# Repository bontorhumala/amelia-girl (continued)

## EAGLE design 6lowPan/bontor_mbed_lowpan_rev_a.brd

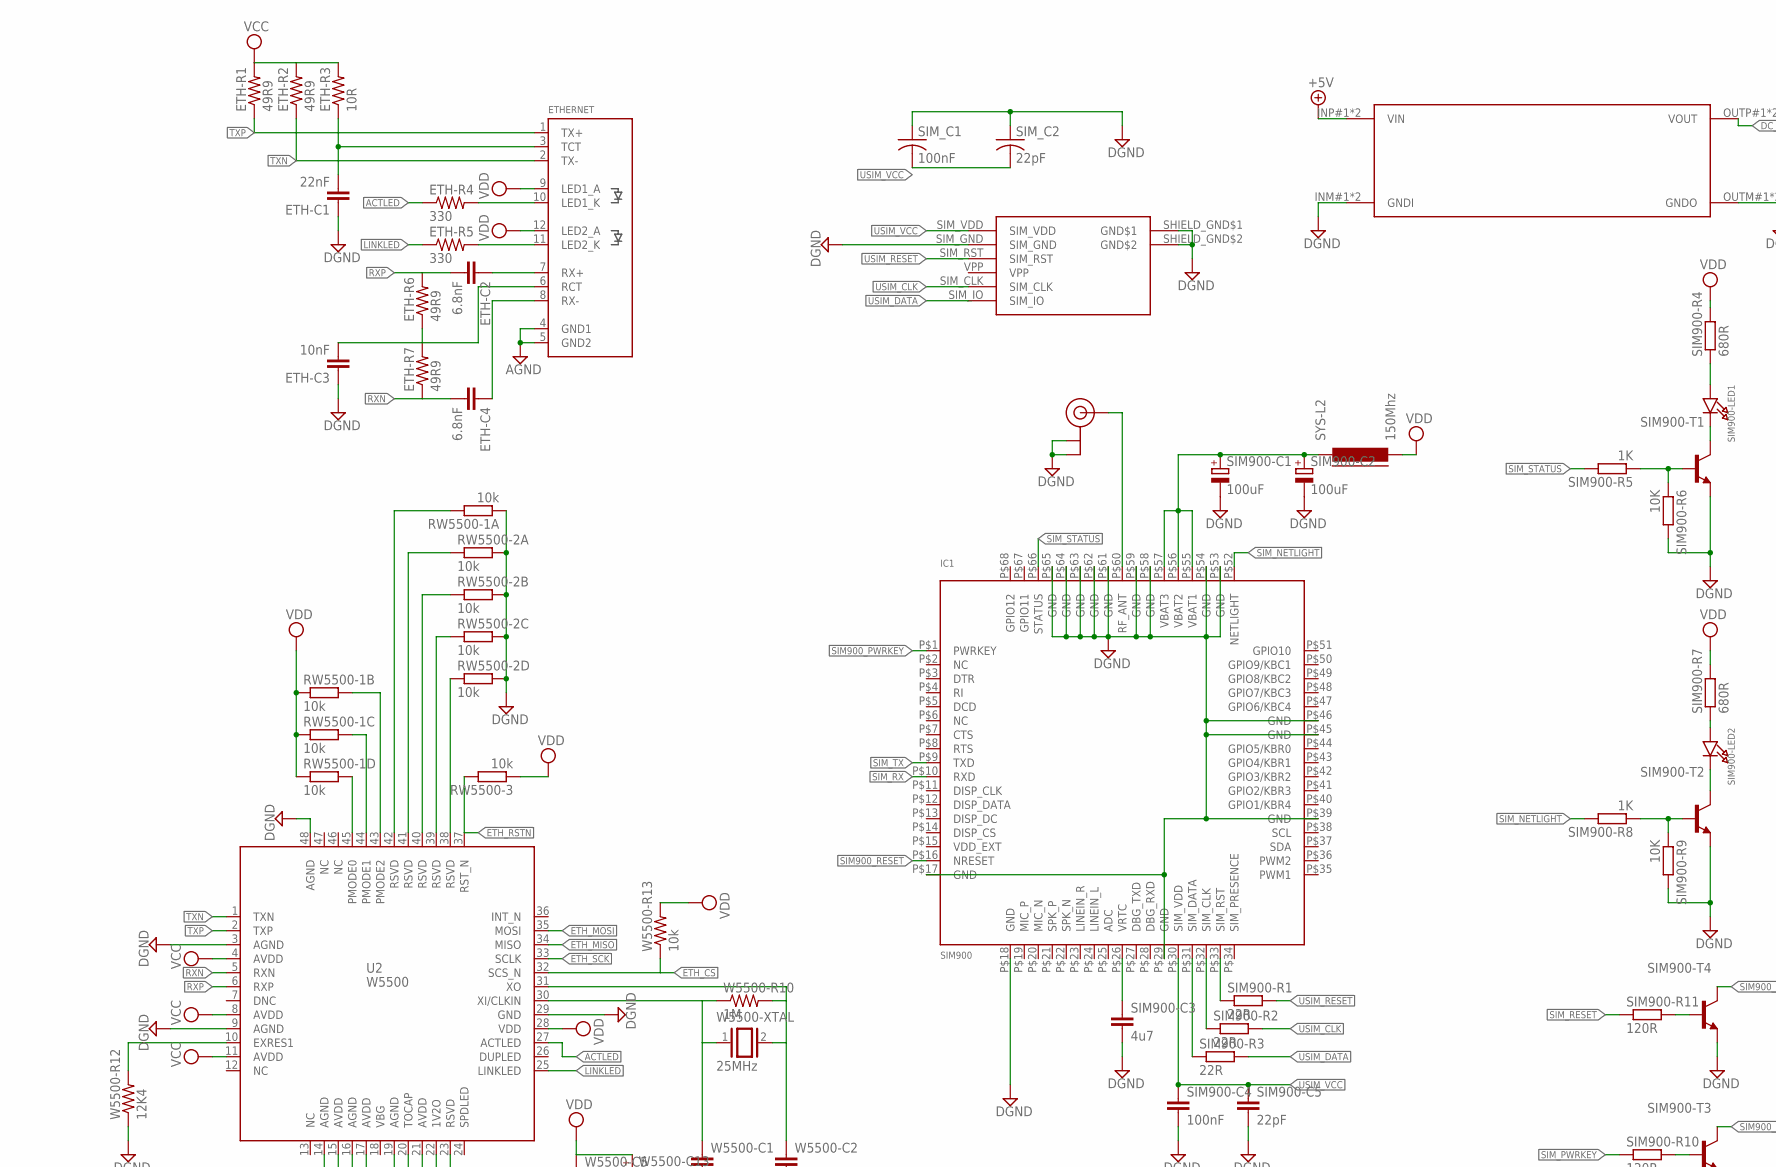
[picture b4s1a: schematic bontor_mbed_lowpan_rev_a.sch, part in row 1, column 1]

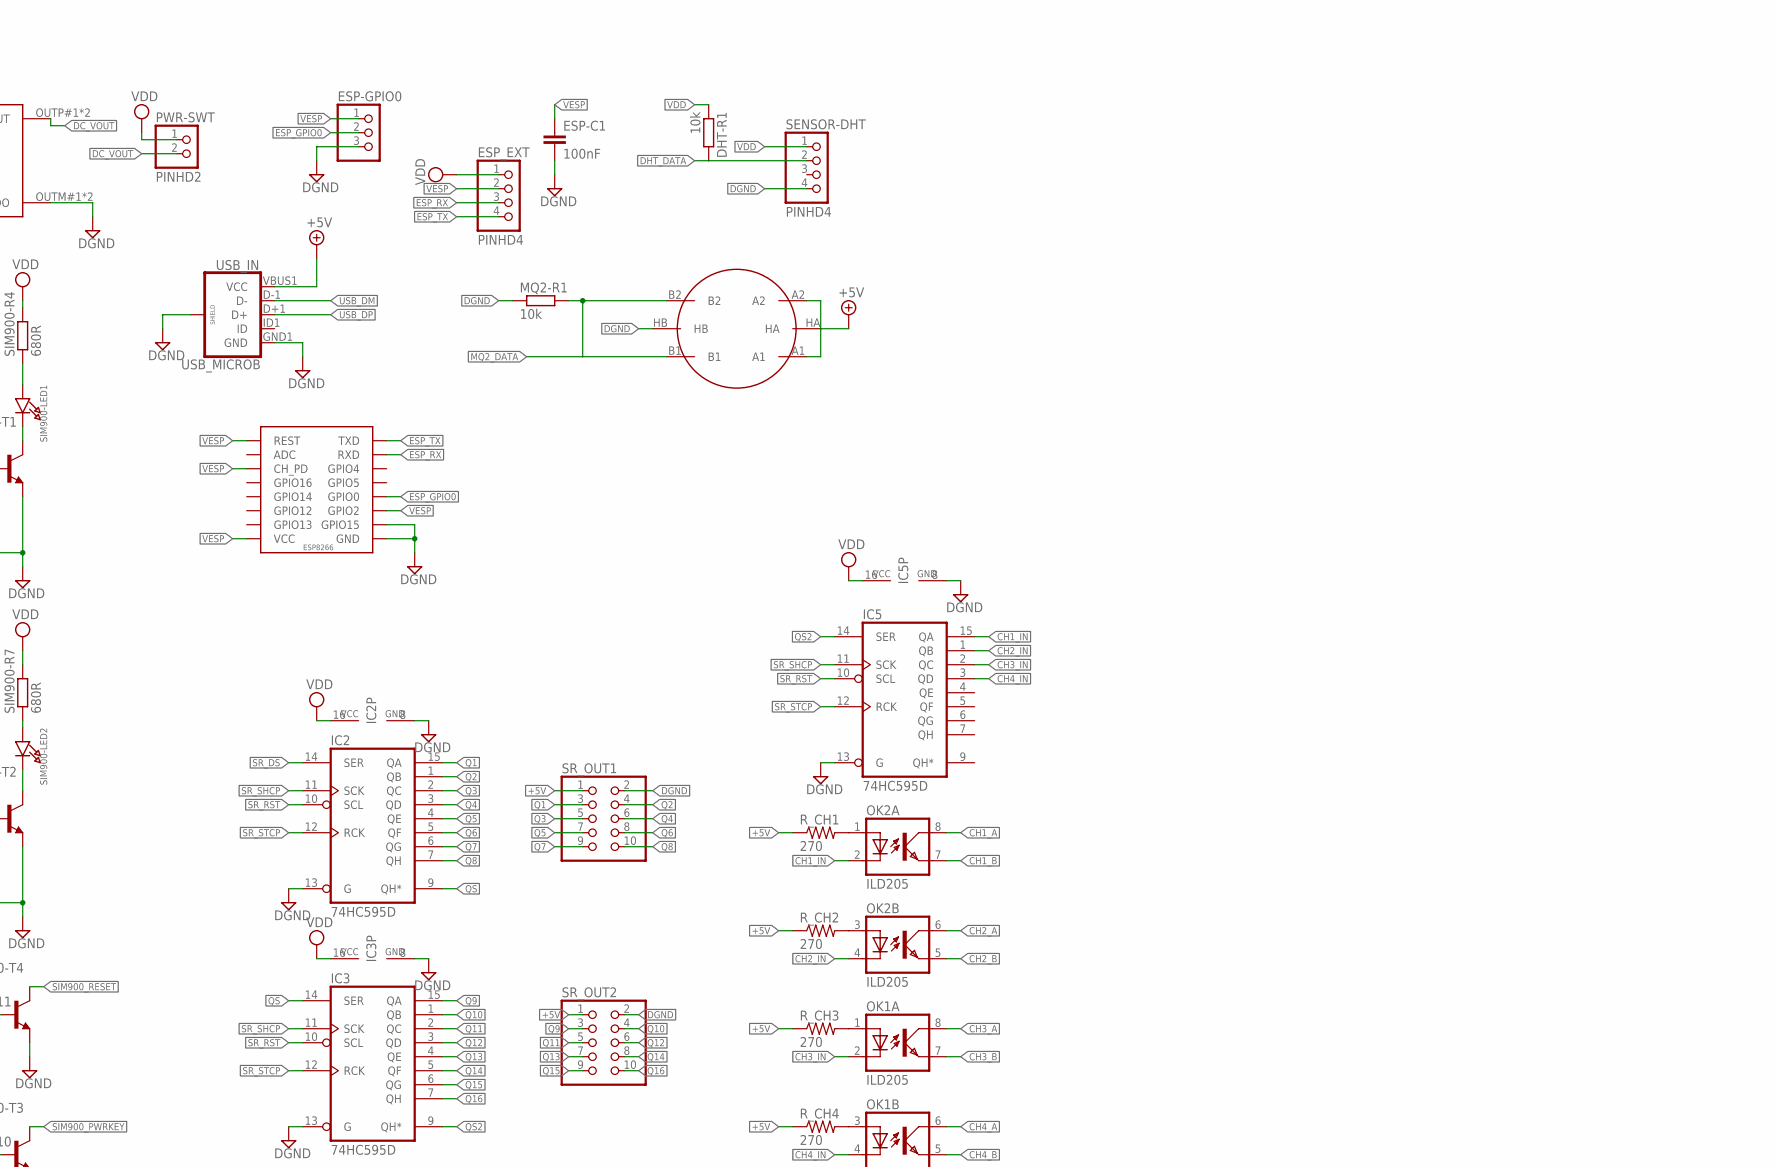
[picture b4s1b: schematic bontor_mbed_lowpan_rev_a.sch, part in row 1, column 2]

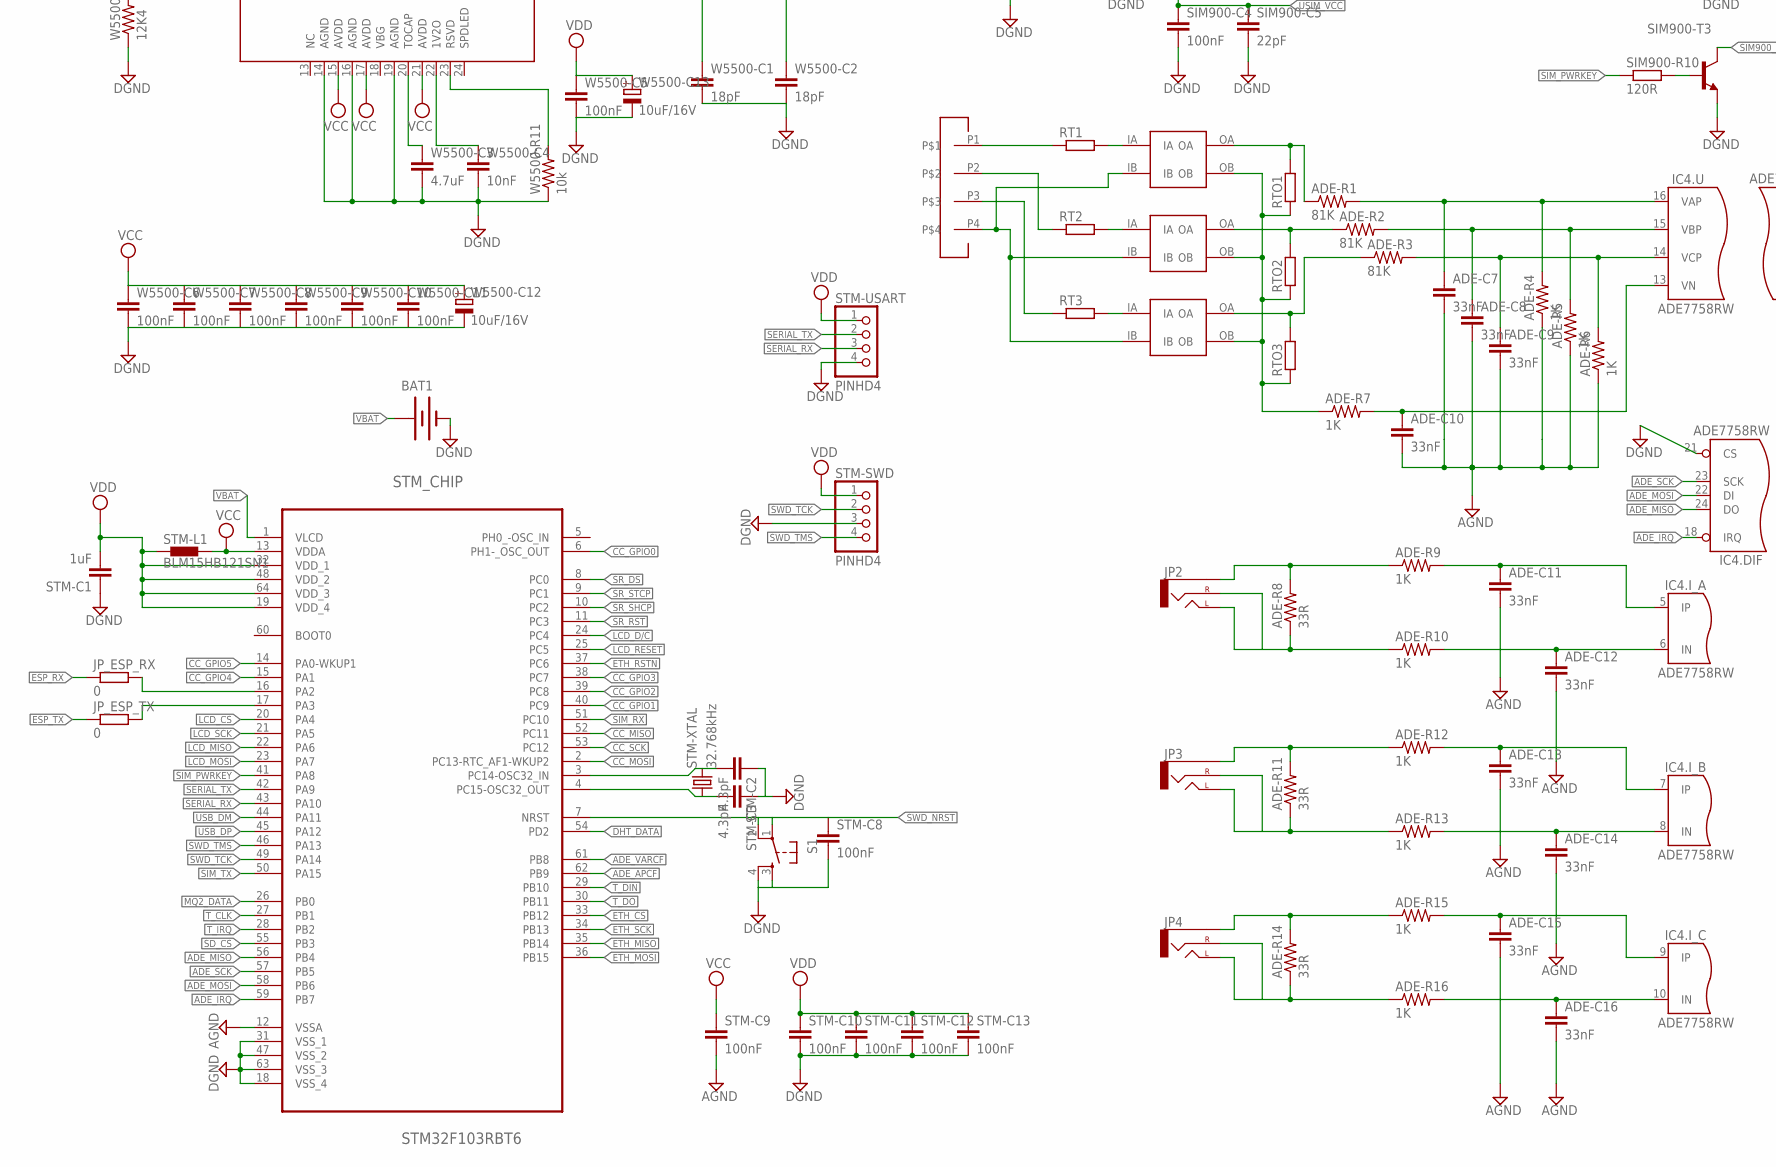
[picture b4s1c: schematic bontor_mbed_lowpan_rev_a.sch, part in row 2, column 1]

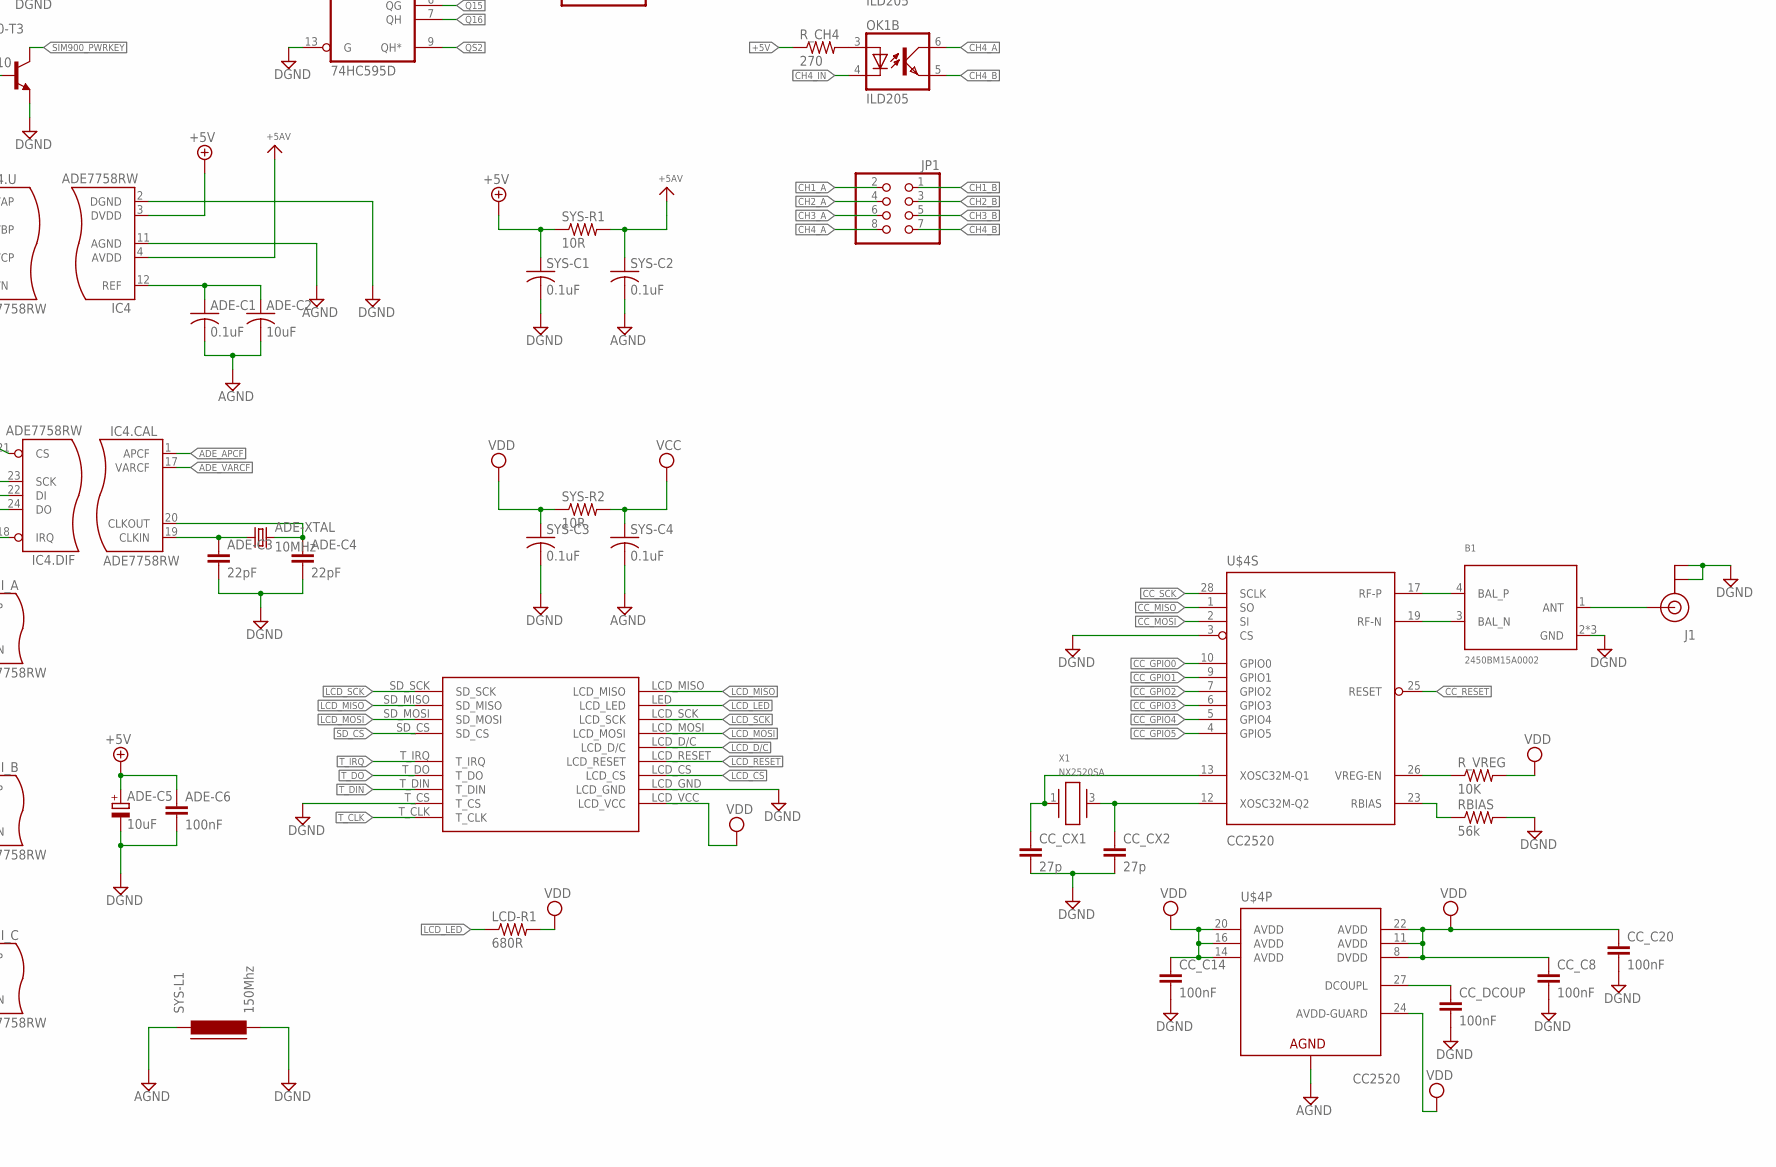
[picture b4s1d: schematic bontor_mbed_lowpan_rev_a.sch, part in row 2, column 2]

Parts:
ADE-C1: 0.1uF; C0603@1
ADE-C2: 10uF; C0805K
ADE-C3, ADE-C4: 22pF; C0603
ADE-C5: 10uF; 153CLV-0605
ADE-C6: 100nF; C0603
ADE-C7, ADE-C8, ADE-C9, ADE-C10, ADE-C11, ADE-C12, ADE-C13, ADE-C14, ADE-C15, ADE-C16: 33nF; 0603-CAP
ADE-R1, ADE-R2, ADE-R3: 81K; 0603-RES
ADE-R4, ADE-R5, ADE-R6, ADE-R7, ADE-R9, ADE-R10, ADE-R12, ADE-R13, ADE-R15, ADE-R16: 1K; 0603-RES
ADE-R8, ADE-R11, ADE-R14: 33R; 0603-RES
ADE-XTAL: 10MHz; HC49US
B1: 2450BM15A0002; 2450BM
BAT1: BATTERY12MM; BATTCON_12MM
CC_C8, CC_C14, CC_C20: 100nF; C0402
CC_CX1, CC_CX2: 27p; C0201
CC_DCOUP: 100nF; C0402
DCDC-3.5V: DCDCMODULE_SMALL; DCDCMODULE-SMALL
DHT-R1: 10k; R0603
ESP-C1: 100nF; C0603
ESP-GPIO0: PINHD-1X3; 1X03
ESP_EXT: PINHD4
ETH-C1: 22nF; C0603
ETH-C2, ETH-C4: 6.8nF; C0603
ETH-C3: 10nF; C0603
ETH-R1, ETH-R2, ETH-R6, ETH-R7: 49R9; R0603
ETH-R3: 10R; R0603
ETH-R4, ETH-R5: 330; R0603
ETHERNET: RJ45J0026D21BNL; RJ45_PULSEJACK
IC1: SIM900; SIM900_SMT
IC2, IC3, IC5: 74HC595D; SO16
IC4: ADE7758RW; SOIC24
J1: U.FL
JP1: PINHD-2X4; 2X04
JP2, JP3, JP4: AUDIO-JACKSMD2; AUDIO-JACK-3.5MM-SMD
JP_ESP_RX: 0; R0201
JP_ESP_TX: 0; R0201
LCD-R1: 680R; 0603-RES
MQ2-R1: 10k; R0603
OK1, OK2: ILD205; SOIC08
PWR-SWT: PINHD2
RBIAS: 56k; 0402-RES
RT1, RT2, RT3: R-EU_0309/V; 0309V
RTO1, RTO2, RTO3: R-EU_0309/12; 0309/12
RW5500-1, RW5500-2: 10k; RN8P-4R-CRA06S
RW5500-3: 10k; R0603
R_CH1, R_CH2, R_CH3, R_CH4: 270; 0603-RES
R_VREG: 10K; 0402-RES
S1: TAC_SWITCHSMD; TACTILE-SWITCH-SMD
SENSOR-DHT: PINHD4
SENSOR-MQ2: METHANE_SENSOR; MQ-3
SIM900-C1, SIM900-C2: 100uF; 153CLV-0605
SIM900-C3: 4u7; C0603
SIM900-C4: 100nF; C0603
SIM900-C5: 22pF; C0603
SIM900-LED1, SIM900-LED2: LED0805_NOOUTLINE; CHIPLED_0805_NOOUTLINE
SIM900-R1, SIM900-R2, SIM900-R3: 22R; R0603
SIM900-R4, SIM900-R7: 680R; R0603
SIM900-R5, SIM900-R8: 1K; R0603
SIM900-R6, SIM900-R9: 10K; R0603
SIM900-R10, SIM900-R11: 120R; R0603
SIM900-T1, SIM900-T2, SIM900-T3, SIM900-T4: MMBT2222ALT1-NPN-SOT23-BEC; SOT23-BEC
SIM_C1: 100nF; C0603K
SIM_C2: 22pF; C0603K
SR_OUT1, SR_OUT2: PINHD-2X5/90; 2X05/90
STM-C1: 1uF; C0603
STM-C2, STM-C3: 4.3pF; C0603
STM-C8, STM-C9, STM-C10, STM-C11, STM-C12, STM-C13: 100nF; C0603
STM-L1: BLM15HB121SN1; 0402
STM-SWD: PINHD4
STM-USART: PINHD4
STM-XTAL: 32.768kHz; TC26H
STM_CHIP: STM32F103RBT6; QFP50P1200X1200X160-64N
SYS-C1, SYS-C2, SYS-C3, SYS-C4: 0.1uF; C0603@1
SYS-L1, SYS-L2: 150Mhz; FB805
SYS-R1, SYS-R2: 10R; 0603-RES
U2: W5500
U$4: CC2520; QFN50P500X500X100-29N
U$5: ESP8266WI12; WI12
U$7: U.FL
U$8: SIM_HOLDER; SIMHOLDER-PUSHPUSH
U$9, U$10, U$11: TRANSFORMER; TV16
U$12: TERMINAL_BLOCK; TERMINAL-RIGHT-ANGLE
U$13: LCD_2.4; LCD_TOUCH_2-4
USB_IN: USB_MICROB; USB-B-MICRO-SMD_V03
W5500-C1, W5500-C2: 18pF; C0603
W5500-C3: 4.7uF; C0603
W5500-C4: 10nF; C0603
W5500-C5, W5500-C6, W5500-C7, W5500-C8, W5500-C9, W5500-C10, W5500-C11: 100nF; C0603
W5500-C12, W5500-C13: 10uF/16V; 153CLV-0605
W5500-R10: 1M; R0603
W5500-R11, W5500-R13: 10k; R0603
W5500-R12: 12K4; R0805
W5500-XTAL: 25MHz; QS
X1: NX2520SA

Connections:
+5V: ADE-C5.+, ADE-C6.1, DCDC-3.5V.INP#1 (VIN), DCDC-3.5V.INP#2 (VIN), IC4.3 (DVDD), R_CH1.1, R_CH2.1, R_CH3.1, R_CH4.1, SENSOR-MQ2.A1, SENSOR-MQ2.A2, SENSOR-MQ2.HA, SR_OUT1.1, SR_OUT2.1, SYS-C1.1, SYS-R1.1, USB_IN.VBUS1 (VCC)
ACTLED: ETH-R4.1, U2.27 (ACTLED)
ADE_APCF: IC4.1 (APCF), STM_CHIP.62 (PB9)
ADE_IRQ: IC4.18 (IRQ), STM_CHIP.59 (PB7)
ADE_MISO: IC4.24 (DO), STM_CHIP.56 (PB4)
ADE_MOSI: IC4.22 (DI), STM_CHIP.58 (PB6)
ADE_SCK: IC4.23 (SCK), STM_CHIP.57 (PB5)
ADE_VARCF: IC4.17 (VARCF), STM_CHIP.61 (PB8)
AGND: ADE-C1.2, ADE-C2.2, ADE-C7.2, ADE-C8.2, ADE-C9.2, ADE-C10.2, ADE-C11.2, ADE-C12.2, ADE-C13.2, ADE-C14.2, ADE-C15.2, ADE-C16.2, ADE-R4.1, ADE-R5.1, ADE-R6.1, ETHERNET.4 (GND1), ETHERNET.5 (GND2), IC4.11 (AGND), STM-C9.2, STM_CHIP.12 (VSSA), SYS-C2.2, SYS-C4.2, SYS-L1.1, U$4.29 (AGND)
AVDD: IC4.4 (AVDD), SYS-C2.1, SYS-R1.2
CC_GPIO0: STM_CHIP.6 (PH1-_OSC_OUT), U$4.10 (GPIO0)
CC_GPIO1: STM_CHIP.40 (PC9), U$4.9 (GPIO1)
CC_GPIO2: STM_CHIP.39 (PC8), U$4.7 (GPIO2)
CC_GPIO3: STM_CHIP.38 (PC7), U$4.6 (GPIO3)
CC_GPIO4: STM_CHIP.15 (PA1), U$4.5 (GPIO4)
CC_GPIO5: STM_CHIP.14 (PA0-WKUP1), U$4.4 (GPIO5)
CC_MISO: STM_CHIP.52 (PC11), U$4.1 (SO)
CC_MOSI: STM_CHIP.2 (PC13-RTC_AF1-WKUP2), U$4.2 (SI)
CC_RESET: U$4.25 (RESET)
CC_SCK: STM_CHIP.53 (PC12), U$4.28 (SCLK)
CH1_A: JP1.2, OK2.8 (COL)
CH1_B: JP1.1, OK2.7 (EMIT)
CH1_IN: IC5.15 (QA), OK2.2 (C)
CH2_A: JP1.4, OK2.6 (COL)
CH2_B: JP1.3, OK2.5 (EMIT)
CH2_IN: IC5.1 (QB), OK2.4 (C)
CH3_A: JP1.6, OK1.8 (COL)
CH3_B: JP1.5, OK1.7 (EMIT)
CH3_IN: IC5.2 (QC), OK1.2 (C)
CH4_A: JP1.8, OK1.6 (COL)
CH4_B: JP1.7, OK1.5 (EMIT)
CH4_IN: IC5.3 (QD), OK1.4 (C)
DC_VOUT: DCDC-3.5V.OUTP#1 (VOUT), DCDC-3.5V.OUTP#2 (VOUT), PWR-SWT.2
DGND: ADE-C3.2, ADE-C4.2, ADE-C5.-, ADE-C6.2, B1.2 (GND), B1.5 (GND), B1.6 (GND), BAT1.GND (-), CC_C8.2, CC_C14.2, CC_C20.2, CC_CX1.2, CC_CX2.2, CC_DCOUP.2, DCDC-3.5V.INM#1 (GNDI), DCDC-3.5V.INM#2 (GNDI), DCDC-3.5V.OUTM#1 (GNDO), DCDC-3.5V.OUTM#2 (GNDO), ESP-C1.2, ESP-GPIO0.3, ETH-C1.1, ETH-C3.1, IC1.P$17 (GND), IC1.P$18 (GND), IC1.P$29 (GND), IC1.P$39 (GND), IC1.P$45 (GND), IC1.P$46 (GND), IC1.P$53 (GND), IC1.P$54 (GND), IC1.P$58 (GND), IC1.P$59 (GND), IC1.P$61 (GND), IC1.P$62 (GND), IC1.P$63 (GND), IC1.P$64 (GND), IC1.P$65 (GND), IC2.8 (GND), IC2.13 (G), IC3.8 (GND), IC3.13 (G), IC4.2 (DGND), IC4.21 (CS), IC5.8 (GND), IC5.13 (G), J1.P$1 (GND), J1.P$2 (GND), MQ2-R1.1, RBIAS.2, RW5500-1.1, RW5500-2.5 (2), RW5500-2.6 (2), RW5500-2.7 (2), RW5500-2.8 (2), S1.3, S1.4, SENSOR-DHT.4, SENSOR-MQ2.HB, SIM900-C1.-, SIM900-C2.-, SIM900-C3.2, SIM900-C4.2, SIM900-C5.2, SIM900-R6.2, SIM900-R9.2, SIM900-T1.E, SIM900-T2.E, SIM900-T3.E, SIM900-T4.E, SIM_C1.1, SIM_C2.1, SR_OUT1.2, SR_OUT2.2, STM-C1.1, STM-C2.1, STM-C3.1, STM-C8.2, STM-C10.2, STM-C11.2, STM-C12.2, STM-C13.2, STM-SWD.3, STM-USART.4, STM_CHIP.18 (VSS_4), STM_CHIP.31 (VSS_1), STM_CHIP.47 (VSS_2), STM_CHIP.63 (VSS_3), SYS-C1.2, SYS-C3.2, SYS-L1.2, U2.3 (AGND), U2.9 (AGND), U2.14 (AGND), U2.16 (AGND), U2.19 (AGND), U2.29 (GND), U2.48 (AGND), U$4.3 (CS), U$5.GND, U$5.GPIO15, U$7.P$1 (GND), U$7.P$2 (GND), U$8.SHIELD_GND$1 (GND$1), U$8.SHIELD_GND$2 (GND$2), U$8.SIM_GND, U$13.LCD_GND, U$13.T_CS, USB_IN.GND1 (GND), USB_IN.SHIELD1 (SHIELD), USB_IN.SHIELD2 (SHIELD), USB_IN.SHIELD3 (SHIELD), W5500-C1.2, W5500-C2.2, W5500-C3.2, W5500-C4.2, W5500-C5.2, W5500-C6.2, W5500-C7.2, W5500-C8.2, W5500-C9.2, W5500-C10.2, W5500-C11.2, W5500-C12.-, W5500-C13.-, W5500-R11.1, W5500-R12.1
DHT_DATA: DHT-R1.2, SENSOR-DHT.2, STM_CHIP.54 (PD2)
ESP_GPIO0: ESP-GPIO0.2, U$5.GPIO00 (GPIO0)
ESP_RX: ESP_EXT.3, JP_ESP_RX.1, U$5.RXD
ESP_TX: ESP_EXT.4, JP_ESP_TX.1, U$5.TXD
ETH_CS: STM_CHIP.33 (PB12), U2.32 (SCS_N), W5500-R13.1
ETH_MISO: STM_CHIP.35 (PB14), U2.34 (MISO)
ETH_MOSI: STM_CHIP.36 (PB15), U2.35 (MOSI)
ETH_RSTN: RW5500-3.2, STM_CHIP.37 (PC6), U2.37 (RST_N)
ETH_SCK: STM_CHIP.34 (PB13), U2.33 (SCLK)
GPIO11: IC1.P$67 (GPIO11)
GPIO12: IC1.P$68 (GPIO12)
IBN: ADE-R11.1, ADE-R13.1, JP3.RING (RIGHT), JP3.TIP (LEFT)
ICN: ADE-R14.1, ADE-R16.1, JP4.RING (RIGHT), JP4.TIP (LEFT)
LCD_CS: STM_CHIP.20 (PA4), U$13.LCD_CS
LCD_D/C: STM_CHIP.24 (PC4), U$13.LCD_D/C
LCD_LED: LCD-R1.1, U$13.LED (LCD_LED)
LCD_MISO: STM_CHIP.22 (PA6), U$13.LCD_MISO, U$13.SD_MISO
LCD_MOSI: STM_CHIP.23 (PA7), U$13.LCD_MOSI, U$13.SD_MOSI
LCD_RESET: STM_CHIP.25 (PC5), U$13.LCD_RESET
LCD_SCK: STM_CHIP.21 (PA5), U$13.LCD_SCK, U$13.SD_SCK
LINKLED: ETH-R5.1, U2.25 (LINKLED)
MQ2_DATA: MQ2-R1.2, SENSOR-MQ2.B1, SENSOR-MQ2.B2, STM_CHIP.26 (PB0)
unnamed: STM-C2.2, STM-XTAL.2, STM_CHIP.3 (PC14-OSC32_IN)
unnamed: STM-C3.2, STM-XTAL.1, STM_CHIP.4 (PC15-OSC32_OUT)
unnamed: IC1.P$31 (SIM_DATA), SIM900-R3.1
unnamed: OK2.1 (A), R_CH1.2
unnamed: OK2.3 (A), R_CH2.2
unnamed: OK1.1 (A), R_CH3.2
unnamed: IC1.P$32 (SIM_CLK), SIM900-R2.1
unnamed: R_VREG.1, U$4.26 (VREG-EN)
unnamed: ADE-C9.1, ADE-R3.2, ADE-R6.2, IC4.14 (VCP)
unnamed: ETH-R4.2, ETHERNET.10 (LED1_K)
unnamed: ETH-R5.2, ETHERNET.11 (LED2_K)
unnamed: IC1.P$33 (SIM_RST), SIM900-R1.1
unnamed: IC1.P$26 (VRTC), SIM900-C3.1
unnamed: IC1.P$60 (RF_ANT), U$7.P$3 (SIGNAL)
unnamed: SIM900-LED1.A, SIM900-R4.1
unnamed: SIM900-LED1.C, SIM900-T1.C
unnamed: SIM900-R5.1, SIM900-R6.1, SIM900-T1.B
unnamed: SIM900-LED2.A, SIM900-R7.1
unnamed: SIM900-LED2.C, SIM900-T2.C
unnamed: SIM900-R8.1, SIM900-R9.1, SIM900-T2.B
unnamed: ETH-C2.1, ETHERNET.7 (RX+)
unnamed: ETH-C1.2, ETH-R3.1, ETHERNET.3 (TCT)
unnamed: ADE-C15.1, ADE-R15.2, IC4.9 (IP)
unnamed: ADE-R11.2, ADE-R12.1, JP3.SLEEVE
unnamed: ETH-C4.1, ETHERNET.8 (RX-)
unnamed: ADE-C11.1, ADE-R9.2, IC4.5 (IP)
unnamed: ADE-C12.1, ADE-R10.2, IC4.6 (IN)
unnamed: ETH-C3.2, ETH-R6.1, ETH-R7.2, ETHERNET.6 (RCT)
unnamed: ADE-C14.1, ADE-R13.2, IC4.8 (IN)
unnamed: ADE-C13.1, ADE-R12.2, IC4.7 (IP)
unnamed: ADE-C1.1, ADE-C2.1, IC4.12 (REF)
unnamed: ADE-C3.1, ADE-XTAL.1, IC4.19 (CLKIN)
unnamed: ADE-C4.1, ADE-XTAL.2, IC4.20 (CLKOUT)
unnamed: ADE-C10.1, ADE-R7.2, IC4.13 (VN)
unnamed: ADE-R2.1, RTO2.2, U$10.OA
unnamed: ADE-C8.1, ADE-R2.2, ADE-R5.2, IC4.15 (VBP)
unnamed: U2.20 (TOCAP), W5500-C3.1
unnamed: ADE-R8.2, ADE-R9.1, JP2.SLEEVE
unnamed: ADE-C16.1, ADE-R16.2, IC4.10 (IN)
unnamed: U2.22 (1V2O), W5500-C4.1
unnamed: U2.23 (RSVD), W5500-R11.2
unnamed: CC_DCOUP.1, U$4.27 (DCOUPL)
unnamed: SIM900-R10.2, SIM900-T3.B
unnamed: SIM900-R11.2, SIM900-T4.B
unnamed: OK1.3 (A), R_CH4.2
unnamed: ADE-R8.1, ADE-R10.1, JP2.RING (RIGHT), JP2.TIP (LEFT)
unnamed: ADE-R14.2, ADE-R15.1, JP4.SLEEVE
unnamed: U2.31 (XO), W5500-C2.1, W5500-R10.2, W5500-XTAL.2
unnamed: U2.10 (EXRES1), W5500-R12.2
unnamed: ADE-C7.1, ADE-R1.2, ADE-R4.2, IC4.16 (VAP)
unnamed: ADE-R1.1, RTO1.2, U$9.OA
unnamed: ADE-R7.1, RTO1.1, RTO2.1, RTO3.1, U$9.OB, U$10.OB, U$11.OB
unnamed: RW5500-2.4 (1), U2.38 (RSVD)
unnamed: RW5500-2.3 (1), U2.39 (RSVD)
unnamed: RW5500-2.2 (1), U2.40 (RSVD)
unnamed: RW5500-2.1, U2.41 (RSVD)
unnamed: RW5500-1.8 (2), U2.42 (RSVD)
unnamed: RW5500-1.7 (2), U2.43 (PMODE2)
unnamed: RW5500-1.6 (2), U2.44 (PMODE1)
unnamed: RW5500-1.5 (2), U2.45 (PMODE0)
unnamed: ADE-R3.1, RTO3.2, U$11.OA
unnamed: U2.30 (XI/CLKIN), W5500-C1.1, W5500-R10.1, W5500-XTAL.1
unnamed: IC1.P$55 (VBAT1), IC1.P$56 (VBAT2), IC1.P$57 (VBAT3), SIM900-C1.+, SIM900-C2.+, SYS-L2.1
unnamed: CC_CX1.1, U$4.13 (XOSC32M-Q1), X1.1
unnamed: CC_CX2.1, U$4.12 (XOSC32M-Q2), X1.3 (2)
unnamed: JP_ESP_RX.2, STM_CHIP.16 (PA2)
unnamed: JP_ESP_TX.2, STM_CHIP.17 (PA3)
unnamed: RT3.2, U$11.IA
unnamed: RT2.2, U$10.IA
unnamed: RT1.2, U$9.IA
unnamed: RBIAS.1, U$4.23 (RBIAS)
unnamed: U$9.IB, U$10.IB, U$11.IB, U$12.P4
unnamed: B1.4 (BAL_P), U$4.17 (RF-P)
unnamed: RT1.1, U$12.P1
unnamed: RT2.1, U$12.P2
unnamed: RT3.1, U$12.P3
unnamed: B1.3 (BAL_N), U$4.19 (RF-N)
unnamed: B1.1 (ANT), J1.P$3 (SIGNAL)
Q1: IC2.15 (QA), SR_OUT1.3
Q2: IC2.1 (QB), SR_OUT1.4
Q3: IC2.2 (QC), SR_OUT1.5
Q4: IC2.3 (QD), SR_OUT1.6
Q5: IC2.4 (QE), SR_OUT1.7
Q6: IC2.5 (QF), SR_OUT1.8
Q7: IC2.6 (QG), SR_OUT1.9
Q8: IC2.7 (QH), SR_OUT1.10
Q9: IC3.15 (QA), SR_OUT2.3
Q10: IC3.1 (QB), SR_OUT2.4
Q11: IC3.2 (QC), SR_OUT2.5
Q12: IC3.3 (QD), SR_OUT2.6
Q13: IC3.4 (QE), SR_OUT2.7
Q14: IC3.5 (QF), SR_OUT2.8
Q15: IC3.6 (QG), SR_OUT2.9
Q16: IC3.7 (QH), SR_OUT2.10
QS: IC2.9 (QH*), IC3.14 (SER)
QS2: IC3.9 (QH*), IC5.14 (SER)
RXN: ETH-C4.2, ETH-R7.1, U2.5 (RXN)
RXP: ETH-C2.2, ETH-R6.2, U2.6 (RXP)
SD_CS: STM_CHIP.55 (PB3), U$13.SD_CS
SERIAL_RX: STM-USART.3, STM_CHIP.43 (PA10)
SERIAL_TX: STM-USART.2, STM_CHIP.42 (PA9)
SIM900_PWRKEY: IC1.P$1 (PWRKEY), SIM900-T3.C
SIM900_RESET: IC1.P$16 (NRESET), SIM900-T4.C
SIM_NETLIGHT: IC1.P$52 (NETLIGHT), SIM900-R8.2
SIM_PWRKEY: SIM900-R10.1, STM_CHIP.41 (PA8)
SIM_RESET: SIM900-R11.1
SIM_RX: IC1.P$10 (RXD), STM_CHIP.51 (PC10)
SIM_STATUS: IC1.P$66 (STATUS), SIM900-R5.2
SIM_TX: IC1.P$9 (TXD), STM_CHIP.50 (PA15)
SR_DS: IC2.14 (SER), STM_CHIP.8 (PC0)
SR_RST: IC2.10 (SCL), IC3.10 (SCL), IC5.10 (SCL), STM_CHIP.11 (PC3)
SR_SHCP: IC2.11 (SCK), IC3.11 (SCK), IC5.11 (SCK), STM_CHIP.10 (PC2)
SR_STCP: IC2.12 (RCK), IC3.12 (RCK), IC5.12 (RCK), STM_CHIP.9 (PC1)
SWD_NRST: S1.1, S1.2, STM-C8.1, STM_CHIP.7 (NRST)
SWD_TCK: STM-SWD.2, STM_CHIP.49 (PA14)
SWD_TMS: STM-SWD.4, STM_CHIP.46 (PA13)
TXN: ETH-R2.1, ETHERNET.2 (TX-), U2.1 (TXN)
TXP: ETH-R1.1, ETHERNET.1 (TX+), U2.2 (TXP)
T_CLK: STM_CHIP.27 (PB1), U$13.T_CLK
T_DIN: STM_CHIP.29 (PB10), U$13.T_DIN
T_DO: STM_CHIP.30 (PB11), U$13.T_DO
T_IRQ: STM_CHIP.28 (PB2), U$13.T_IRQ
USB_DM: STM_CHIP.44 (PA11), USB_IN.D-1 (D-)
USB_DP: STM_CHIP.45 (PA12), USB_IN.D+1 (D+)
USIM_CLK: SIM900-R2.2, U$8.SIM_CLK
USIM_DATA: SIM900-R3.2, U$8.SIM_IO
USIM_RESET: SIM900-R1.2, U$8.SIM_RST
USIM_VCC: IC1.P$30 (SIM_VDD), SIM900-C4.1, SIM900-C5.1, SIM_C1.2, SIM_C2.2, U$8.SIM_VDD
VBAT: BAT1.PWR@1 (+), STM_CHIP.1 (VLCD)
VCC: ETH-R1.2, ETH-R2.2, ETH-R3.2, STM-C9.1, STM-L1.2, STM_CHIP.13 (VDDA), SYS-C4.1, SYS-R2.2, U2.4 (AVDD), U2.8 (AVDD), U2.11 (AVDD), U2.15 (AVDD), U2.17 (AVDD), U2.21 (AVDD), W5500-C6.1, W5500-C7.1, W5500-C8.1, W5500-C9.1, W5500-C10.1, W5500-C11.1, W5500-C12.+
VDD: CC_C8.1, CC_C14.1, CC_C20.1, DHT-R1.1, ESP_EXT.1, ETHERNET.9 (LED1_A), ETHERNET.12 (LED2_A), IC2.16 (VCC), IC3.16 (VCC), IC5.16 (VCC), LCD-R1.2, PWR-SWT.1, RW5500-1.2 (1), RW5500-1.3 (1), RW5500-1.4 (1), RW5500-3.1, R_VREG.2, SENSOR-DHT.1, SIM900-R4.2, SIM900-R7.2, STM-C1.2, STM-C10.1, STM-C11.1, STM-C12.1, STM-C13.1, STM-L1.1, STM-SWD.1, STM-USART.1, STM_CHIP.19 (VDD_4), STM_CHIP.32 (VDD_1), STM_CHIP.48 (VDD_2), STM_CHIP.64 (VDD_3), SYS-C3.1, SYS-L2.2, SYS-R2.1, U2.28 (VDD), U$4.8 (DVDD), U$4.11 (AVDD), U$4.14 (AVDD), U$4.16 (AVDD), U$4.20 (AVDD), U$4.22 (AVDD), U$4.24 (AVDD-GUARD), U$13.LCD_VCC, W5500-C5.1, W5500-C13.+, W5500-R13.2
VESP: ESP-C1.1, ESP-GPIO0.1, ESP_EXT.2, U$5.CH_PD, U$5.GPIO02 (GPIO2), U$5.REST, U$5.VCC

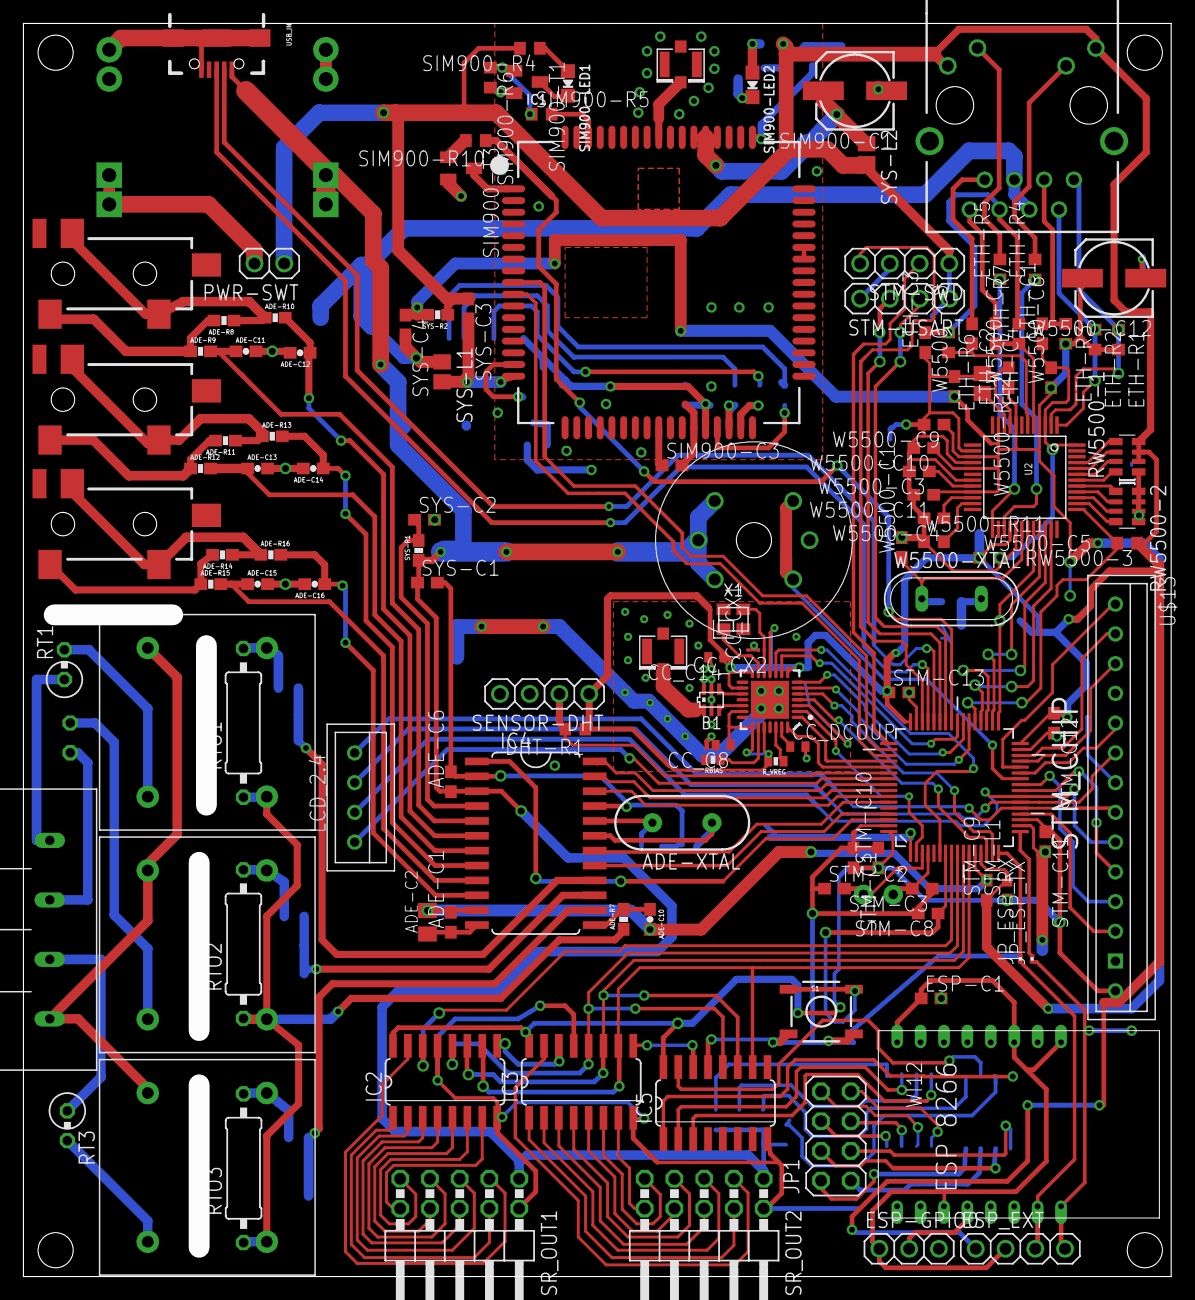
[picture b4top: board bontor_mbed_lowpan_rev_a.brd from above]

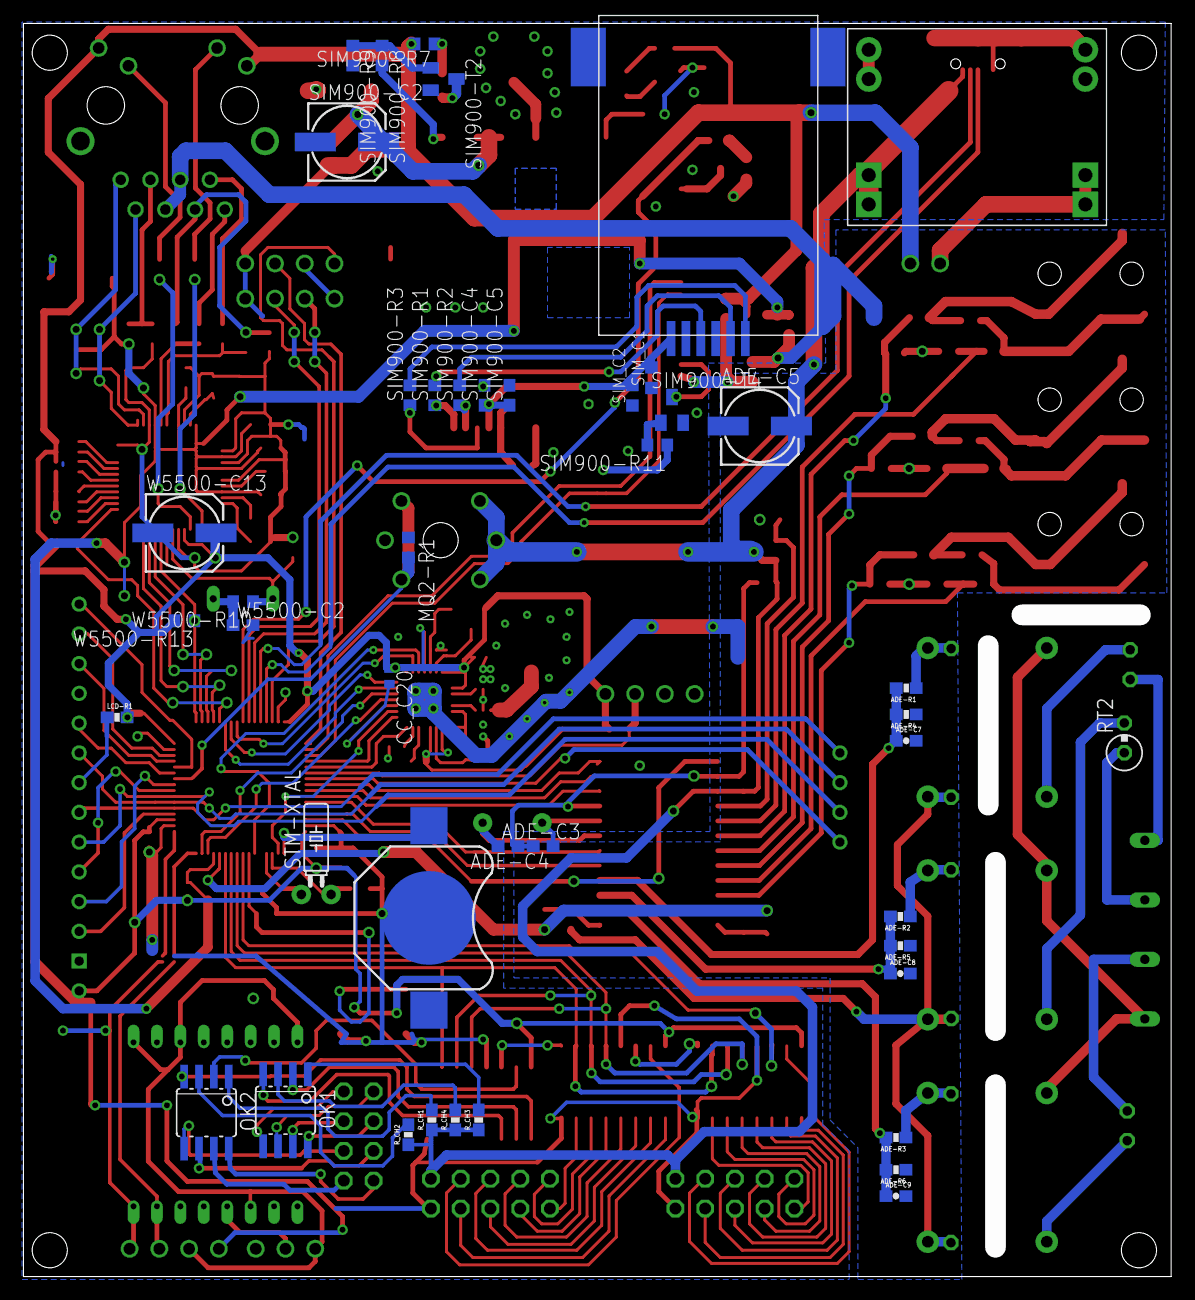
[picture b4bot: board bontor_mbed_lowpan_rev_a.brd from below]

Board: 2 copper layers, 98.0 x 107.0 mm, 171 parts (44 on the bottom side), 184 nets.

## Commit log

2015-05-15 add gerber and BoM
2015-05-19 added PCB models and revise PCB to move DC module on top
2015-05-20 update all PCB design
2015-05-26 adding designators and center components on its origin
2015-05-27 update PCB and BoM to use vertical RJ11
2015-05-27 update PCB and BoM and model to use vertical RJ11
2015-05-28 use RJ11 vertical connector
2015-06-09 update silkscreen and delete USB micro hole
2015-06-12 version g puts lcd directly on pcb
2015-07-24 add mcb enhancer and add power switch on controller
2015-07-24 add mcb enhancer BoM and gerber
2015-08-21 added on off button and remove LCD resstor
2015-11-29 routing mcb-enhancer, not DRC/ERC-ed yet
2015-12-18 repair silkscreen
